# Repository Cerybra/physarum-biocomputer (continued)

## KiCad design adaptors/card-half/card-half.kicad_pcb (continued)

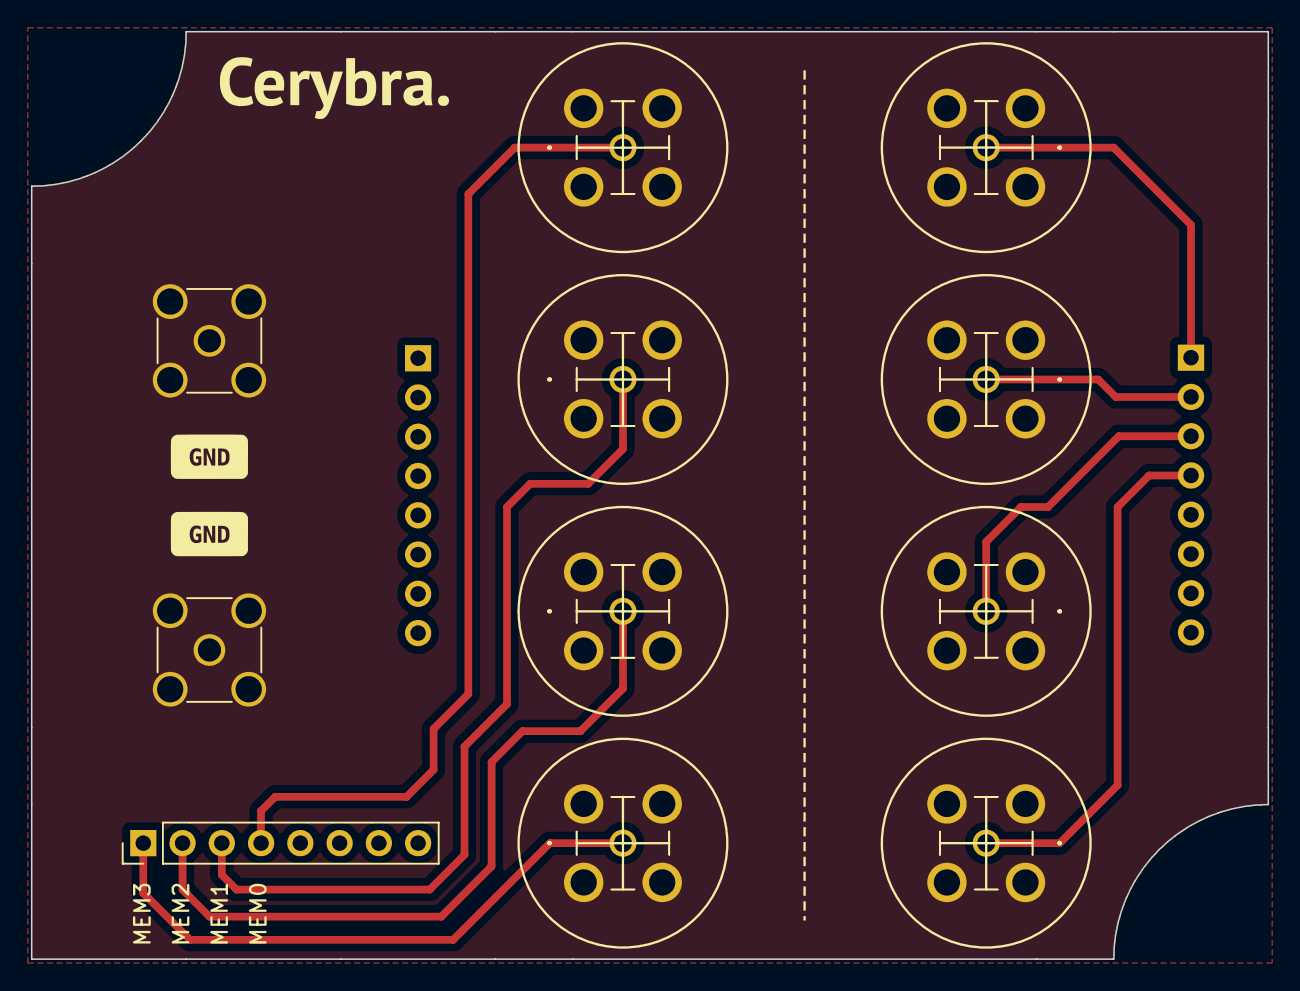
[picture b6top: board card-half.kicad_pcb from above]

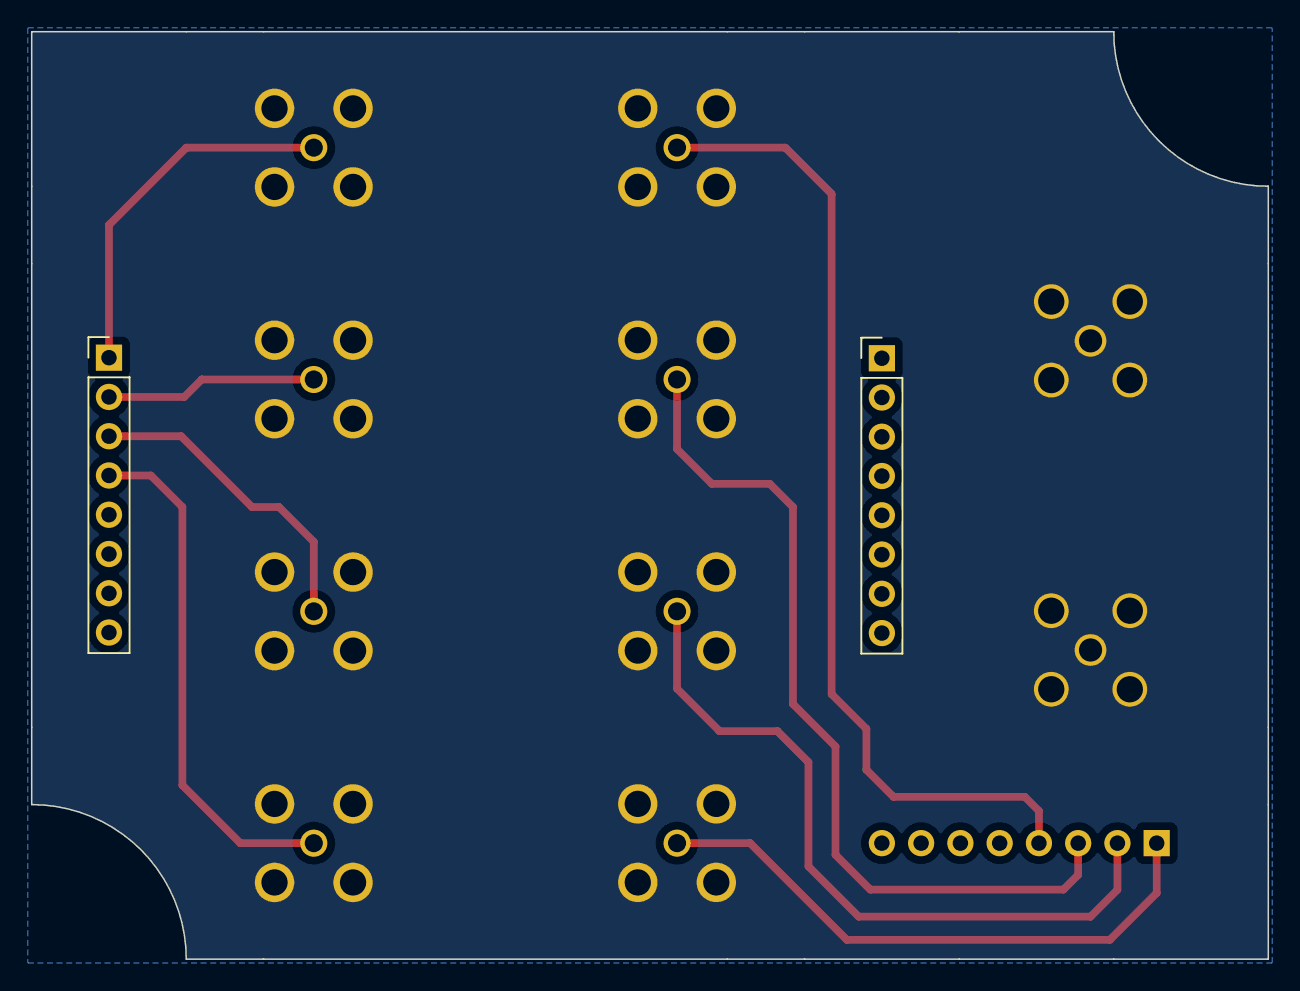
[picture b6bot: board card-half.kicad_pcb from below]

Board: 2 copper layers, 80.0 x 60.0 mm, 13 parts (2 on the bottom side), 9 nets.

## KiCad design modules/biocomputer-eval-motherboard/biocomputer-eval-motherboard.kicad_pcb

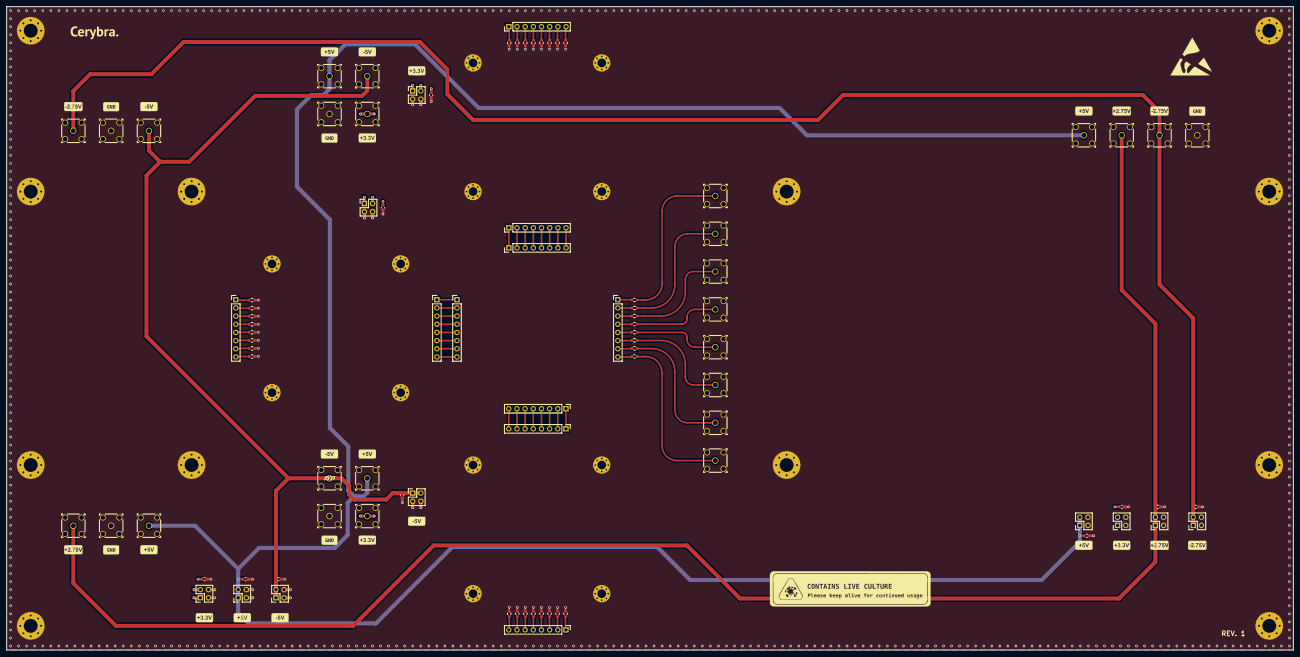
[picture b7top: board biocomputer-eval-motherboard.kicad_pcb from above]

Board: 4 copper layers, 400.0 x 200.0 mm, 113 parts (0 on the bottom side), 62 nets.

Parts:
C301, C302, C303, C304, C401, C501, C601, C602, C603, C604: 100nF; C_0603_1608Metric
H101, H102, H103, H104, H201, H202, H203, H204, H601, H602, H603, H604: MountingHole_Pad; MountingHole_4.3mm_M4_Pad_Via
H301, H302, H303, H304, H401, H402, H403, H404, H501, H502, H503, H504: MountingHole_Pad; MountingHole_2.7mm_M2.5_Pad_Via
J101, J102, J103, J104, J105, J106, J107, J108, J201, J202, J203, J204, J205, J206, J305, J306, J307, J308, J311, J312, J313, J314, J605, J606, J607, J608: Conn_Coaxial; CONN_RF2-04A-T-00-50-G_ADM
J109, J110, J111, J112, J309, J310, J402, J403, J502, J503: Conn_01x08; PinHeader_1x08_P2.54mm_Vertical
J113: Traces; TRACES
J301, J302, J303, J304, J401, J501, J601, J602, J603, J604: Conn_01x04; PinHeader_2x02_P2.54mm_Vertical
R101, R102, R103, R104, R105, R106, R107, R108, R301, R302, R303, R304, R305, R306, R307, R308, R401, R402, R403, R404, R405, R406, R407, R408, R501, R502, R503, R504, R505, R506, R507, R508: 10k; R_0603_1608Metric

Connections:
+2V5: C603.2, J203.1 (In), J603.1, J603.2, J606.1 (In)
+3V3: C301.2, C401.2, C501.2, C602.2, J301.1, J301.2, J305.1 (In), J311.1 (In), J401.1, J401.2, J501.1, J501.2, J602.1, J602.2
+5V: C302.2, C601.2, J201.1 (In), J302.1, J302.2, J306.1 (In), J312.1 (In), J601.1, J601.2, J605.1 (In)
-2V5: C604.2, J206.1 (In), J604.1, J604.2, J607.1 (In)
-5V: C303.2, C304.2, J204.1 (In), J303.1, J303.2, J304.1, J304.2, J307.1 (In), J313.1 (In)
/column-selector/COLUMN_SELECT_0: J111.1, J502.1
/column-selector/COLUMN_SELECT_1: J111.2, J502.2
/column-selector/COLUMN_SELECT_2: J111.3, J502.3
/column-selector/COLUMN_SELECT_3: J111.4, J502.4
/column-selector/COLUMN_SELECT_4: J111.5, J502.5
/column-selector/COLUMN_SELECT_5: J111.6, J502.6
/column-selector/COLUMN_SELECT_6: J111.7, J502.7
/column-selector/COLUMN_SELECT_7: J111.8, J502.8
/crossbar/CROSSBAR_OUT_0: J112.1, R101.1
/crossbar/CROSSBAR_OUT_1: J112.2, R102.1
/crossbar/CROSSBAR_OUT_2: J112.3, R103.1
/crossbar/CROSSBAR_OUT_3: J112.4, R104.1
/crossbar/CROSSBAR_OUT_4: J112.5, R105.1
/crossbar/CROSSBAR_OUT_5: J112.6, R106.1
/crossbar/CROSSBAR_OUT_6: J112.7, R107.1
/crossbar/CROSSBAR_OUT_7: J112.8, R108.1
/crossbar/DAC_INPUT_0: J109.1, J309.1
/crossbar/DAC_INPUT_1: J109.2, J309.2
/crossbar/DAC_INPUT_2: J109.3, J309.3
/crossbar/DAC_INPUT_3: J109.4, J309.4
/crossbar/DAC_INPUT_4: J109.5, J309.5
/crossbar/DAC_INPUT_5: J109.6, J309.6
/crossbar/DAC_INPUT_6: J109.7, J309.7
/crossbar/DAC_INPUT_7: J109.8, J309.8
/crossbar/ROW_SELECT_0: J110.1, J402.1
/crossbar/ROW_SELECT_1: J110.2, J402.2
/crossbar/ROW_SELECT_2: J110.3, J402.3
/crossbar/ROW_SELECT_3: J110.4, J402.4
/crossbar/ROW_SELECT_4: J110.5, J402.5
/crossbar/ROW_SELECT_5: J110.6, J402.6
/crossbar/ROW_SELECT_6: J110.7, J402.7
/crossbar/ROW_SELECT_7: J110.8, J402.8
Earth: C301.1, C302.1, C303.1, C304.1, C401.1, C501.1, C601.1, C602.1, C603.1, C604.1, H101.1, H102.1, H103.1, H104.1, H201.1, H202.1, H203.1, H204.1, H301.1, H302.1, H303.1, H304.1, H401.1, H402.1, H403.1, H404.1, H501.1, H502.1, H503.1, H504.1, H601.1, H602.1, H603.1, H604.1, J101.2 (Ext), J102.2 (Ext), J103.2 (Ext), J104.2 (Ext), J105.2 (Ext), J106.2 (Ext), J107.2 (Ext), J108.2 (Ext), J201.2 (Ext), J202.1 (In), J202.2 (Ext), J203.2 (Ext), J204.2 (Ext), J205.1 (In), J205.2 (Ext), J206.2 (Ext), J301.3, J301.4, J302.3, J302.4, J303.3, J303.4, J304.3, J304.4, J305.2 (Ext), J306.2 (Ext), J307.2 (Ext), J308.1 (In), J308.2 (Ext), J311.2 (Ext), J312.2 (Ext), J313.2 (Ext), J314.1 (In), J314.2 (Ext), J401.3, J401.4, J501.3, J501.4, J601.3, J601.4, J602.3, J602.4, J603.3, J603.4, J604.3, J604.4, J605.2 (Ext), J606.2 (Ext), J607.2 (Ext), J608.1 (In), J608.2 (Ext), R301.2, R302.2, R303.2, R304.2, R305.2, R306.2, R307.2, R308.2, R401.2, R402.2, R403.2, R404.2, R405.2, R406.2, R407.2, R408.2, R501.2, R502.2, R503.2, R504.2, R505.2, R506.2, R507.2, R508.2
unnamed: J310.1, R301.1
unnamed: J310.2, R302.1
unnamed: J310.3, R303.1
unnamed: J310.4, R304.1
unnamed: J310.5, R305.1
unnamed: J310.6, R306.1
unnamed: J310.7, R307.1
unnamed: J310.8, R308.1
unnamed: J403.1, R401.1
unnamed: J403.2, R402.1
unnamed: J403.3, R403.1
unnamed: J403.4, R404.1
unnamed: J403.5, R405.1
unnamed: J403.6, R406.1
unnamed: J403.7, R407.1
unnamed: J403.8, R408.1
unnamed: J503.1, R501.1
unnamed: J503.2, R502.1
unnamed: J503.3, R503.1
unnamed: J503.4, R504.1
unnamed: J503.5, R505.1
unnamed: J503.6, R506.1
unnamed: J503.7, R507.1
unnamed: J503.8, R508.1

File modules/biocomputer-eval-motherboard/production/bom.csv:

Comment,Designator,Footprint,LCSC Part #
100nF Unpolarized capacitor,"C301,C302,C303,C304,C401,C501,C601,C602,C603,C604",C_0603_1608Metric,
"Conn_Coaxial coaxial connector (BNC, SMA, SMB, SMC, Cinch/RCA, LEMO, ...)","J101,J102,J103,J104,J105,J106,J107,J108,J201,J202,J203,J204,J205,J206,J305,J306,J307,J308,J311,J312,J313,J314,J605,J606,J607,J608",CONN_RF2-04A-T-00-50-G_ADM,C496549
"10k Resistor, US symbol","R101,R102,R103,R104,R105,R106,R107,R108,R301,R302,R303,R304,R305,R306,R307,R308,R401,R402,R403,R404,R405,R406,R407,R408,R501,R502,R503,R504,R505,R506,R507,R508",R_0603_1608Metric,

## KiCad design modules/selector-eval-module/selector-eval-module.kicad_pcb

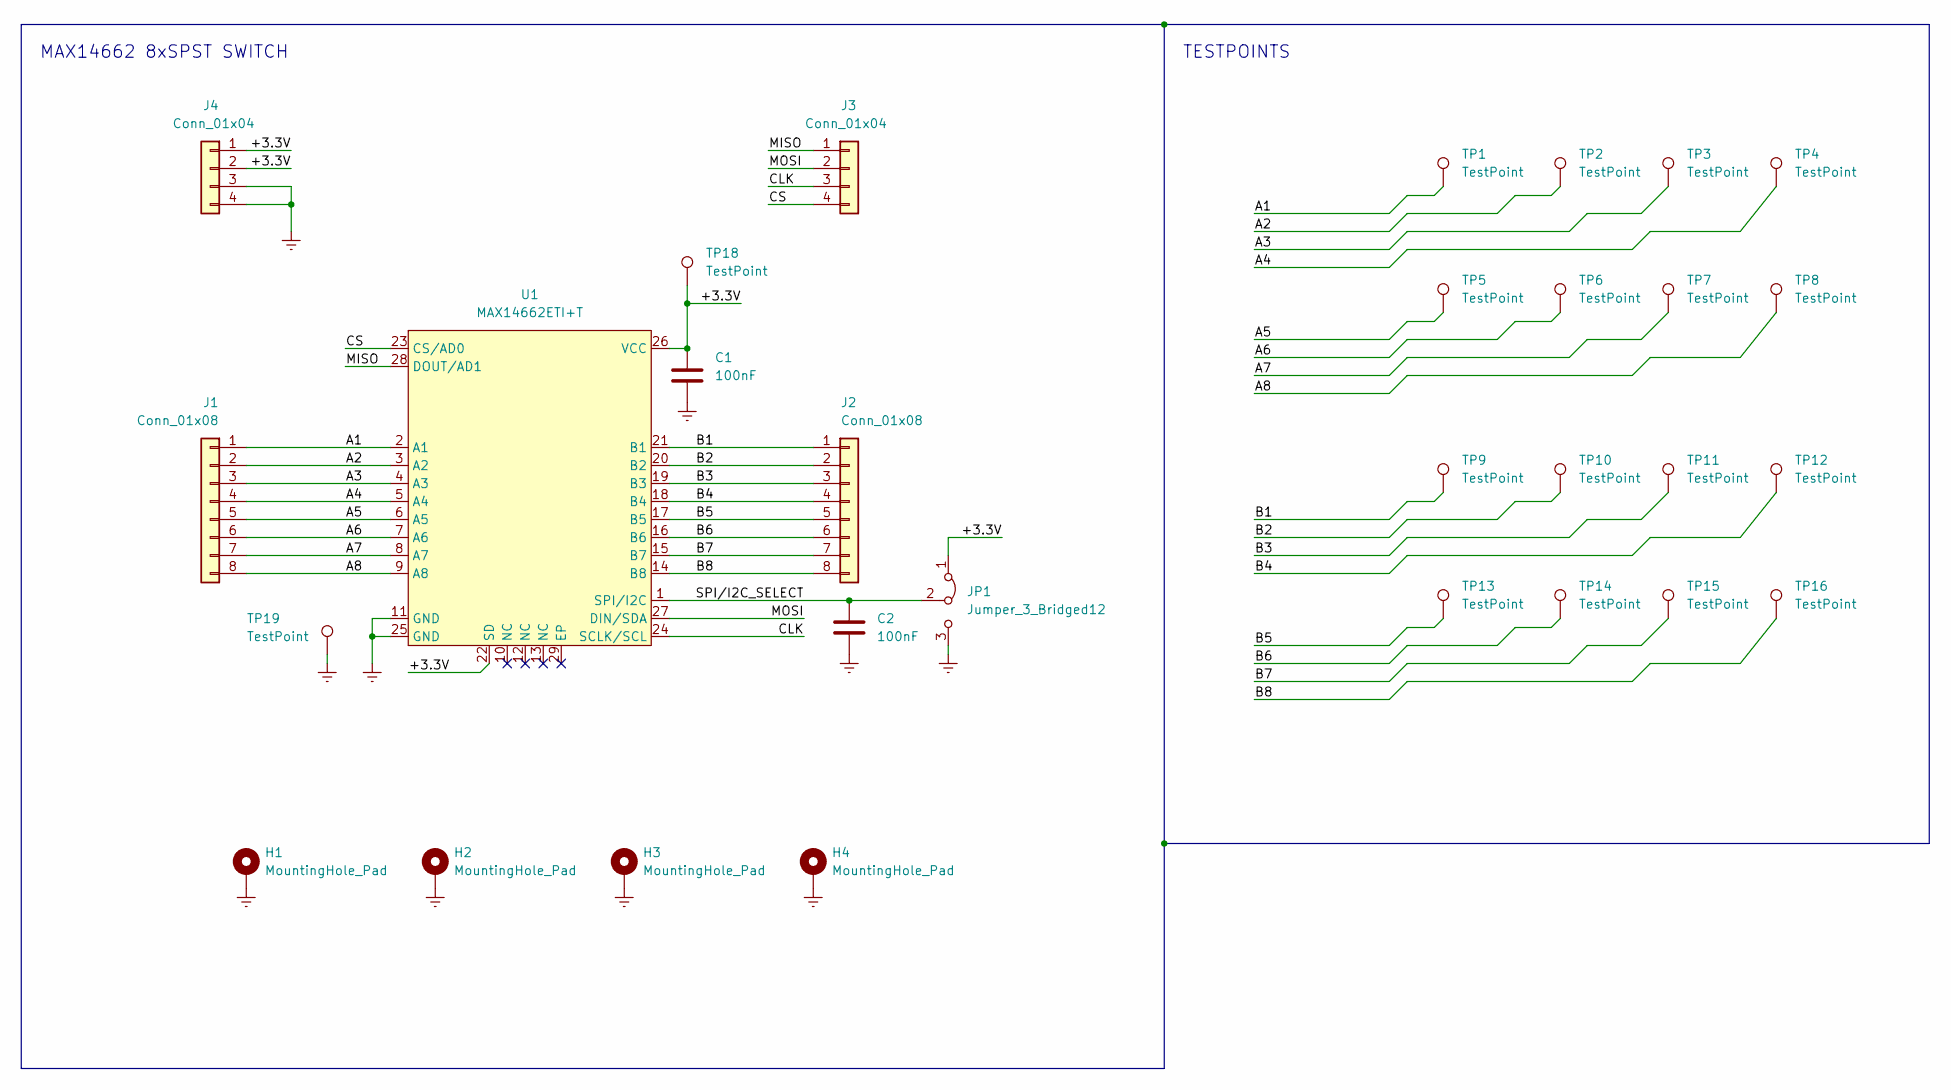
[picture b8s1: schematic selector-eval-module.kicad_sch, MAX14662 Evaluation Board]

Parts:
C1, C2: 100nF; C_0402_1005Metric
H1, H2, H3, H4: MountingHole_Pad; MountingHole_2.7mm_Pad_Via
J1, J2: Conn_01x08; PinSocket_1x08_P2.54mm_Vertical
J3, J4: Conn_01x04; PinHeader_2x02_P2.54mm_Vertical
JP1: Jumper_3_Bridged12; PinHeader_1x03_P2.54mm_Vertical
TP1, TP2, TP3, TP4, TP5, TP6, TP7, TP8, TP9, TP10, TP11, TP12, TP13, TP14, TP15, TP16: TestPoint; KEYSTONE_5002
TP18: TestPoint; KEYSTONE_5000
TP19: TestPoint; KEYSTONE_5006
U1: MAX14662ETI+T; TQFN-28-EP1_4.00x4.00mm_P5.0mm

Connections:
/+3.3V: C1.1, J4.1, J4.2, JP1.1 (A), TP18.1, U1.22 (SD), U1.26 (VCC)
/A1: J1.1, TP1.1, U1.2 (A1)
/A2: J1.2, TP2.1, U1.3 (A2)
/A3: J1.3, TP3.1, U1.4 (A3)
/A4: J1.4, TP4.1, U1.5 (A4)
/A5: J1.5, TP5.1, U1.6 (A5)
/A6: J1.6, TP6.1, U1.7 (A6)
/A7: J1.7, TP7.1, U1.8 (A7)
/A8: J1.8, TP8.1, U1.9 (A8)
/B1: J2.1, TP9.1, U1.21 (B1)
/B2: J2.2, TP10.1, U1.20 (B2)
/B3: J2.3, TP11.1, U1.19 (B3)
/B4: J2.4, TP12.1, U1.18 (B4)
/B5: J2.5, TP13.1, U1.17 (B5)
/B6: J2.6, TP14.1, U1.16 (B6)
/B7: J2.7, TP15.1, U1.15 (B7)
/B8: J2.8, TP16.1, U1.14 (B8)
/CLK: J3.3, U1.24 (SCLK/SCL)
/CS: J3.4, U1.23 (CS/AD0)
/MISO: J3.1, U1.28 (DOUT/AD1)
/MOSI: J3.2, U1.27 (DIN/SDA)
/SPI/I2C_SELECT: C2.1, JP1.2 (C), U1.1 (SPI/I2C)
Earth: C1.2, C2.2, H1.1, H2.1, H3.1, H4.1, J4.3, J4.4, JP1.3 (B), TP19.1, U1.11 (GND), U1.25 (GND)

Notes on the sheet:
MAX14662 8xSPST SWITCH
TESTPOINTS

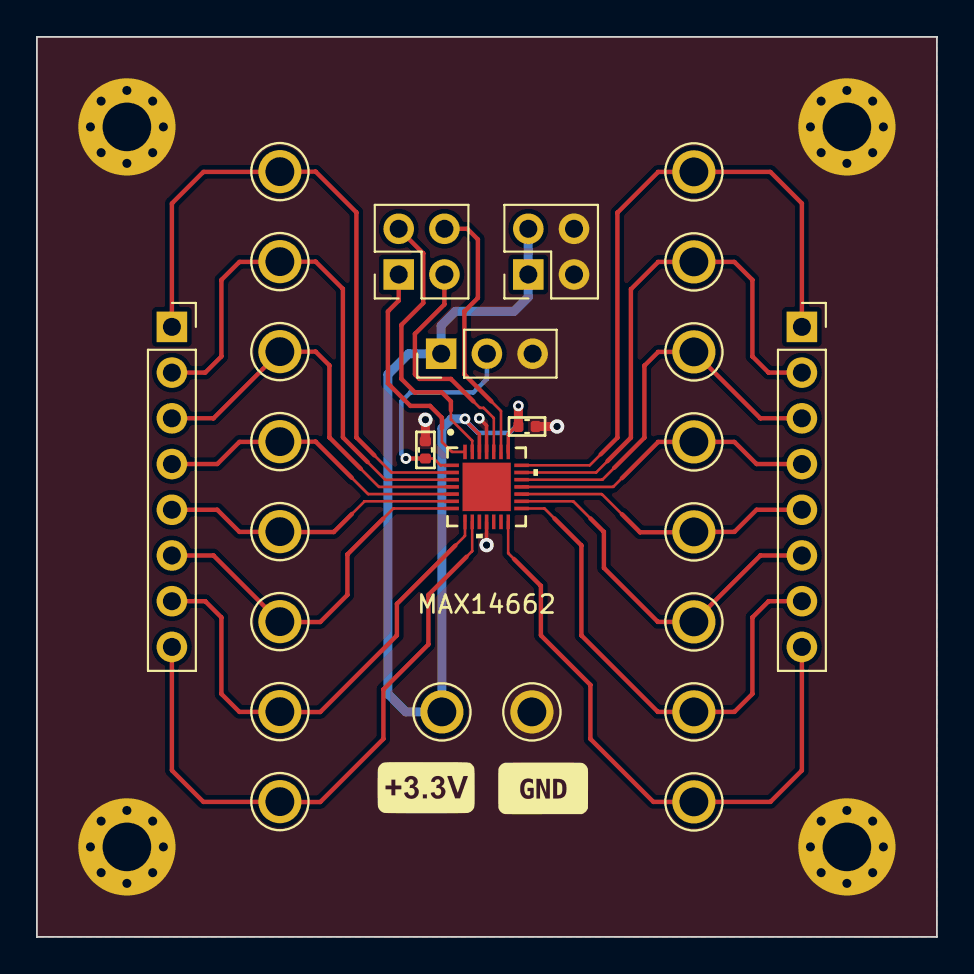
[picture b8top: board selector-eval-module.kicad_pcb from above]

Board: 4 copper layers, 50.0 x 50.0 mm, 30 parts (0 on the bottom side), 23 nets.

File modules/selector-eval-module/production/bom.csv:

Comment,Designator,Footprint,LCSC Part #
100nF Unpolarized capacitor,"C1,C2",C_0402_1005Metric,
TestPoint test point,"TP1,TP2,TP3,TP4,TP5,TP6,TP7,TP8,TP9,TP10,TP11,TP12,TP13,TP14,TP15,TP16",KEYSTONE_5002,
TestPoint test point,TP18,KEYSTONE_5000,
TestPoint test point,TP19,KEYSTONE_5006,
MAX14662ETI+T 8xSPST Switch,U1,TQFN-28-EP1_4.00x4.00mm_P5.0mm,
